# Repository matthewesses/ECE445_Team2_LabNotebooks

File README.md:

# ECE445 Team 2's Lab Notebooks
Lab Notebook repository for Team 2 for ECE 445 at UIUC

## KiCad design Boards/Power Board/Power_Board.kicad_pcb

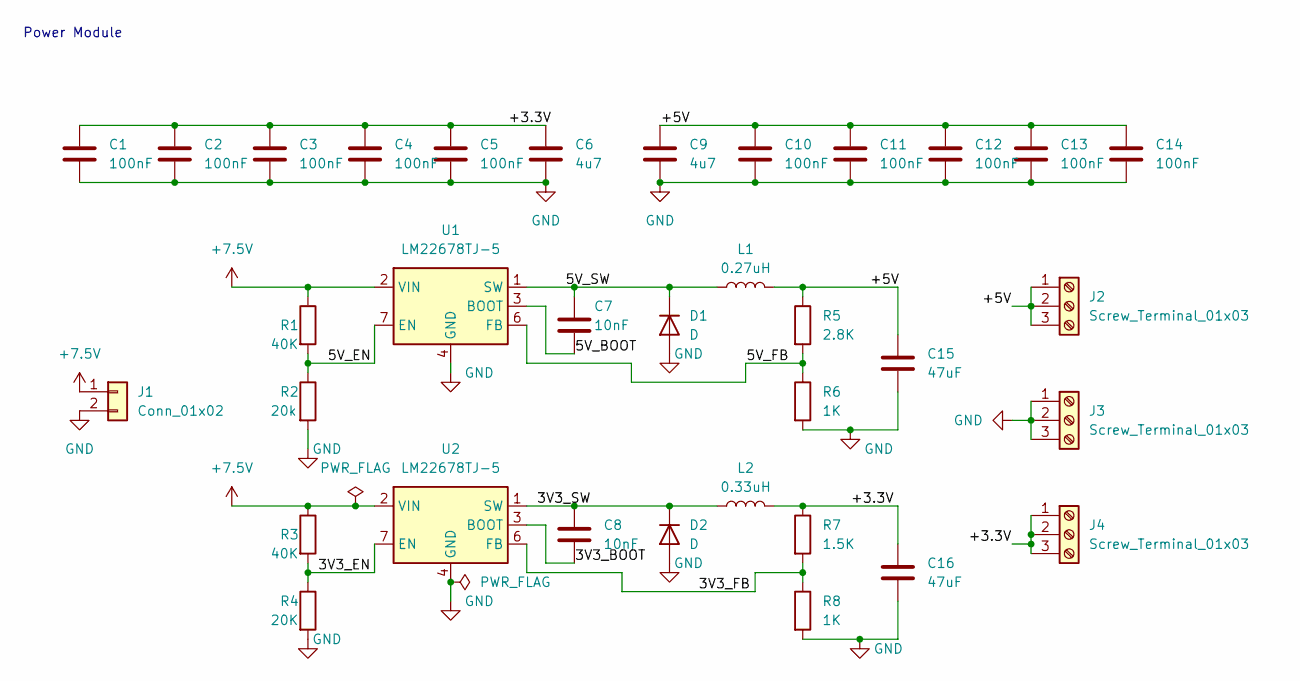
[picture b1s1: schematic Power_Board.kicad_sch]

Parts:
C1, C2, C3, C4, C5, C10, C11, C12, C13, C14: 100nF; C_0805_2012Metric_Pad1.18x1.45mm_HandSolder
C6, C9: 4u7; C_0805_2012Metric_Pad1.18x1.45mm_HandSolder
C7, C8: 10nF; C_0805_2012Metric_Pad1.18x1.45mm_HandSolder
C15, C16: 47uF; C_0805_2012Metric_Pad1.18x1.45mm_HandSolder
D1, D2: D; D_1210_3225Metric_Pad1.42x2.65mm_HandSolder
J1: Conn_01x02; AMASS_XT60-M_1x02_P7.20mm_Vertical
J2, J3, J4: Screw_Terminal_01x03; PinSocket_1x03_P2.54mm_Vertical
L1: 0.27uH; L_1210_3225Metric
L2: 0.33uH; L_1210_3225Metric
R1, R3: 40K; R_0805_2012Metric_Pad1.20x1.40mm_HandSolder
R2: 20k; R_0805_2012Metric_Pad1.20x1.40mm_HandSolder
R4: 20K; R_0805_2012Metric_Pad1.20x1.40mm_HandSolder
R5: 2.8K; R_0805_2012Metric_Pad1.20x1.40mm_HandSolder
R6, R8: 1K; R_0805_2012Metric_Pad1.20x1.40mm_HandSolder
R7: 1.5K; R_0805_2012Metric_Pad1.20x1.40mm_HandSolder
U1, U2: LM22678TJ-5; TO-263-7_TabPin8

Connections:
+7.5V: J1.1, R1.1, R3.1, U1.2 (VIN), U2.2 (VIN)
/3V3_BOOT: C8.2, U2.3 (BOOT)
/3V3_EN: R3.2, R4.1, U2.7 (EN)
/3V3_FB: R7.2, R8.1, U2.6 (FB)
/3V3_SW: C8.1, D2.1 (K), L2.1, U2.1 (SW)
/5V_BOOT: C7.2, U1.3 (BOOT)
/5V_EN: R1.2, R2.1, U1.7 (EN)
/5V_FB: R5.2, R6.1, U1.6 (FB)
/5V_SW: C7.1, D1.1 (K), L1.1, U1.1 (SW)
/+3.3V: C1.1, C2.1, C3.1, C4.1, C5.1, C6.1, C16.1, J4.1, J4.2, J4.3, L2.2, R7.1
/+5V: C9.1, C10.1, C11.1, C12.1, C13.1, C14.1, C15.1, J2.1, J2.2, J2.3, L1.2, R5.1
GND: C1.2, C2.2, C3.2, C4.2, C5.2, C6.2, C9.2, C10.2, C11.2, C12.2, C13.2, C14.2, C15.2, C16.2, D1.2 (A), D2.2 (A), J1.2, J3.1, J3.2, J3.3, R2.2, R4.2, R6.2, R8.2, U1.4 (GND), U1.8 (GND), U2.4 (GND), U2.8 (GND)

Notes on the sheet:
Power Module

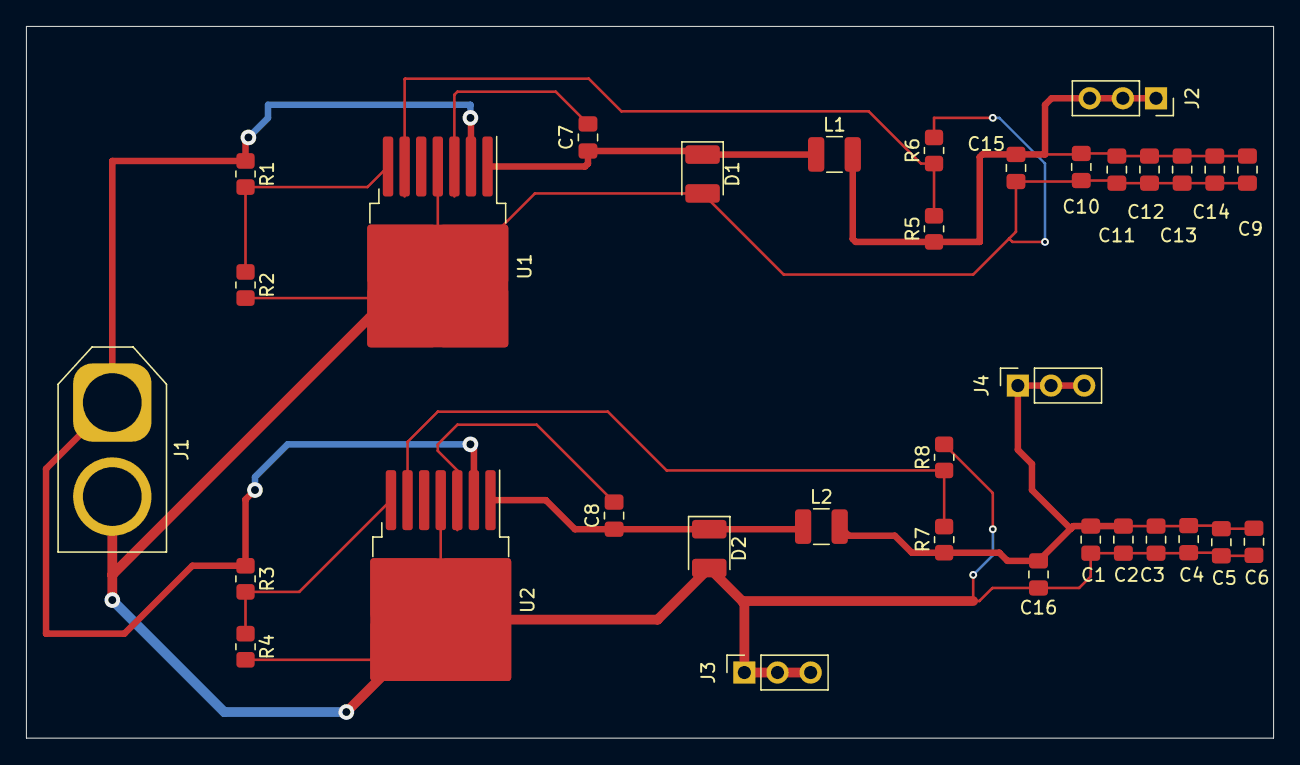
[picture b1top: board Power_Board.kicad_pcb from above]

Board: 2 copper layers, 95.5 x 54.5 mm, 34 parts (0 on the bottom side), 12 nets.

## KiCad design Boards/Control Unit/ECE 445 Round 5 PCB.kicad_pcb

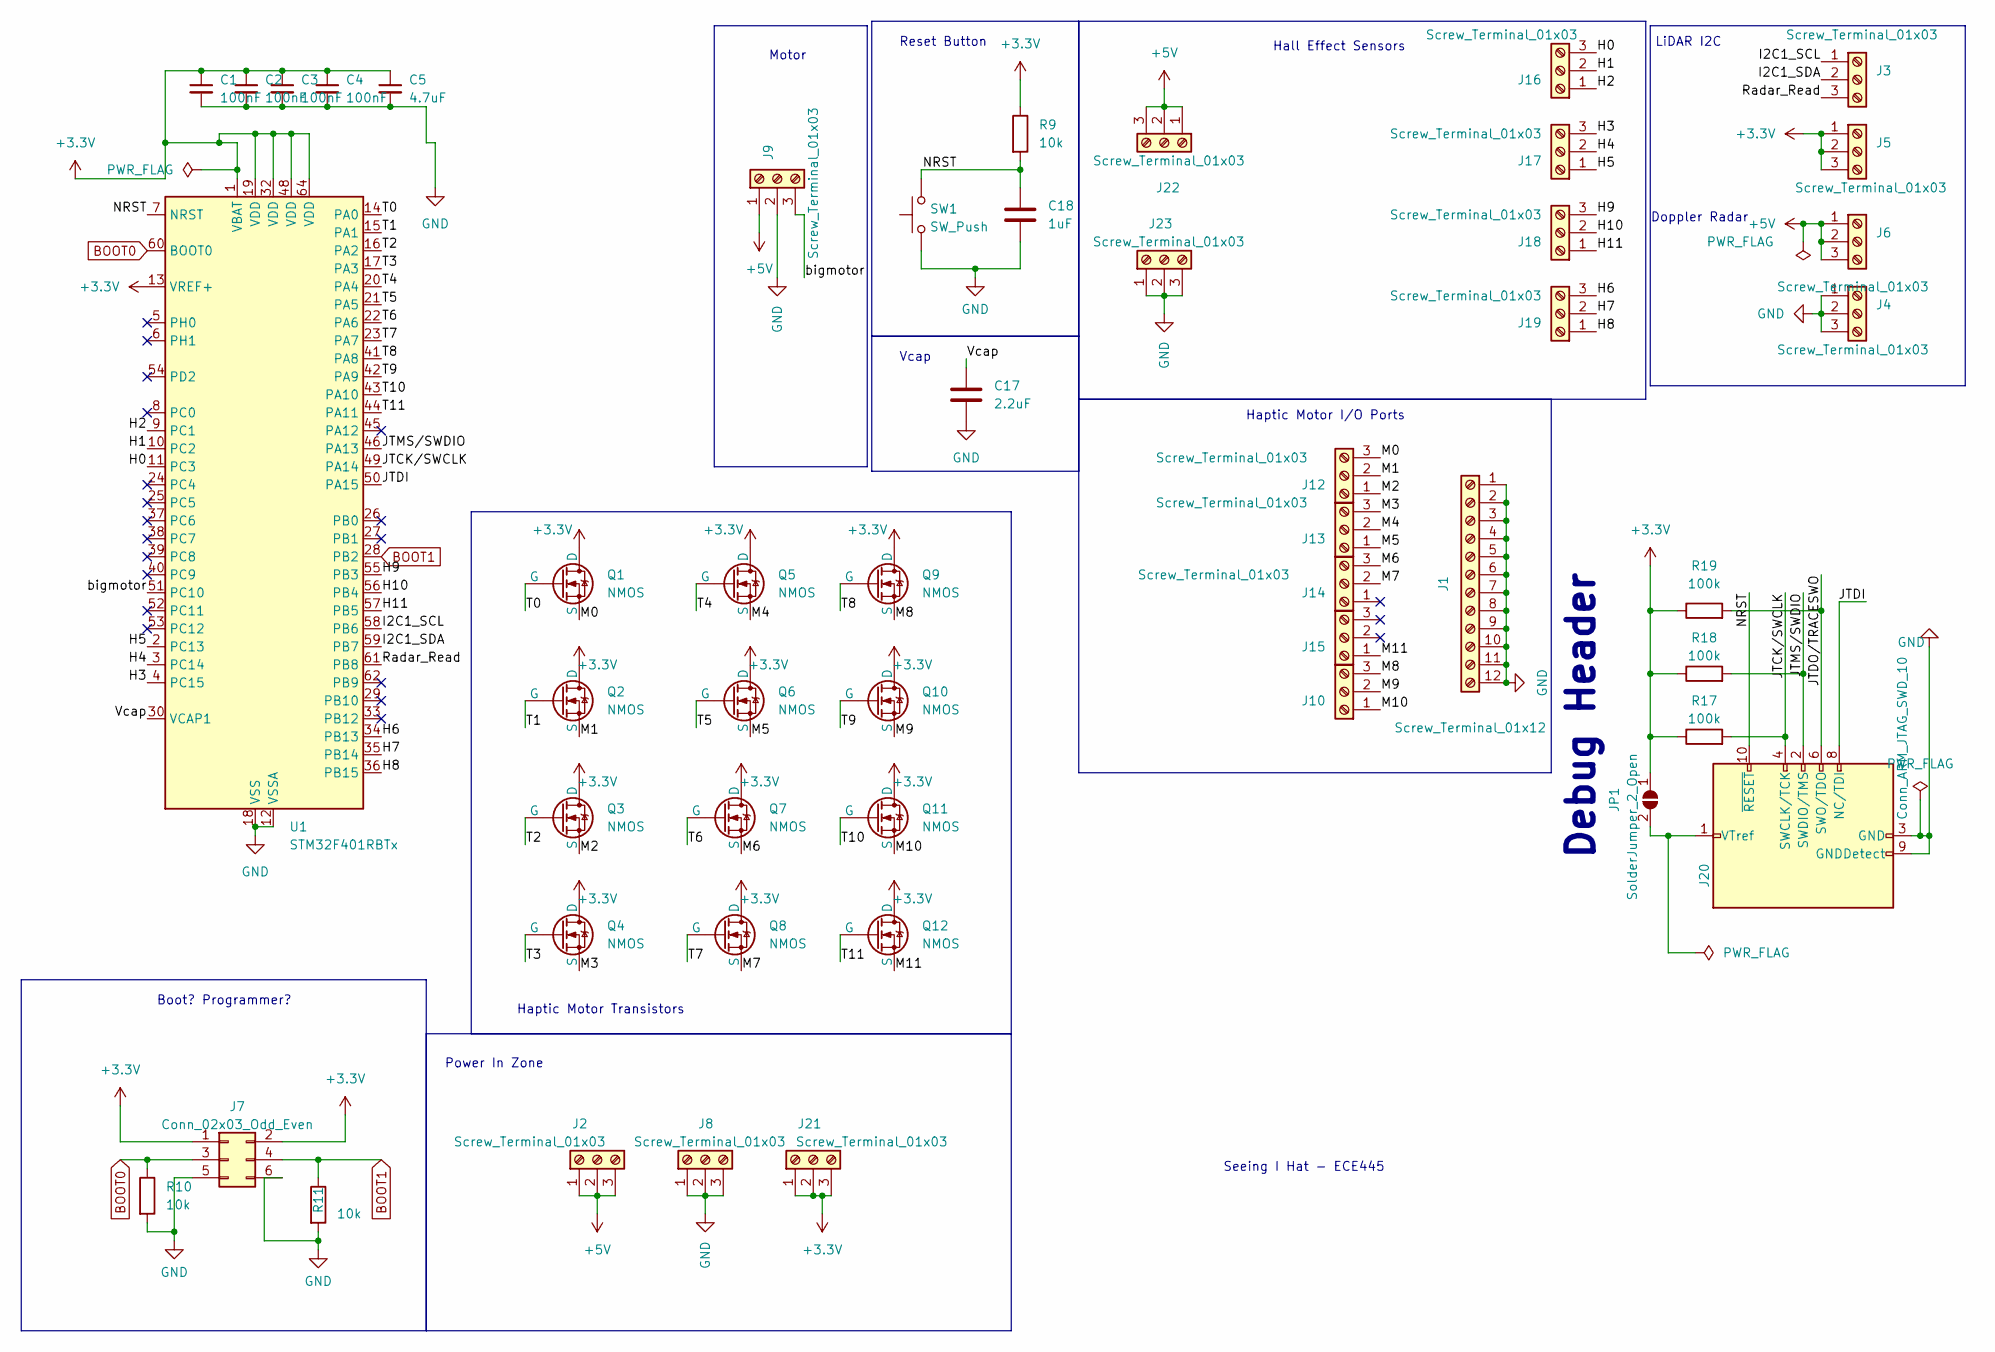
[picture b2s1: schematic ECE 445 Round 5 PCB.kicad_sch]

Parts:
C1, C2, C3, C4: 100nF; C_0805_2012Metric_Pad1.18x1.45mm_HandSolder
C5: 4.7uF; C_0805_2012Metric_Pad1.18x1.45mm_HandSolder
C17: 2.2uF; C_0805_2012Metric_Pad1.18x1.45mm_HandSolder
C18: 1uF; C_0805_2012Metric_Pad1.18x1.45mm_HandSolder
J1: Screw_Terminal_01x12; PinSocket_1x12_P2.54mm_Vertical
J2, J3, J4, J5, J6, J8, J9, J10, J12, J13, J14, J15, J16, J17, J18, J19, J21, J22, J23: Screw_Terminal_01x03; PinSocket_1x03_P2.54mm_Vertical
J7: Conn_02x03_Odd_Even; PinSocket_2x03_P2.54mm_Vertical
J20: Conn_ARM_JTAG_SWD_10; IDC-Header_2x05_P2.54mm_Vertical
JP1: SolderJumper_2_Open; SolderJumper-2_P1.3mm_Open_TrianglePad1.0x1.5mm
Q1, Q2, Q3, Q4, Q5, Q6, Q7, Q8, Q9, Q10, Q11, Q12: NMOS; SOT-23-3
R9, R10, R11: 10k; R_0805_2012Metric_Pad1.20x1.40mm_HandSolder
R17, R18, R19: 100k; R_0805_2012Metric_Pad1.20x1.40mm_HandSolder
SW1: SW_Push; SW_SPST_B3S-1000
U1: STM32F401RBTx; LQFP-64_10x10mm_P0.5mm

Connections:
+3.3V: C1.1, C2.1, C3.1, C4.1, C5.1, J5.1, J5.2, J5.3, J7.1, J7.2, J21.1, J21.2, J21.3, JP1.1 (A), Q1.1 (D), Q2.1 (D), Q3.1 (D), Q4.1 (D), Q5.1 (D), Q6.1 (D), Q7.1 (D), Q8.1 (D), Q9.1 (D), Q10.1 (D), Q11.1 (D), Q12.1 (D), R9.1, R17.1, R18.1, R19.1, U1.1 (VBAT), U1.13 (VREF+), U1.19 (VDD), U1.32 (VDD), U1.48 (VDD), U1.64 (VDD)
+5V: J2.1, J2.2, J2.3, J6.1, J6.2, J6.3, J9.1, J22.1, J22.2, J22.3
/H0: J16.3, U1.11 (PC3)
/H1: J16.2, U1.10 (PC2)
/H2: J16.1, U1.9 (PC1)
/H3: J17.3, U1.4 (PC15)
/H4: J17.2, U1.3 (PC14)
/H5: J17.1, U1.2 (PC13)
/H6: J19.3, U1.34 (PB13)
/H7: J19.2, U1.35 (PB14)
/H8: J19.1, U1.36 (PB15)
/H9: J18.3, U1.55 (PB3)
/H10: J18.2, U1.56 (PB4)
/H11: J18.1, U1.57 (PB5)
/I2C1_SCL: J3.1, U1.58 (PB6)
/I2C1_SDA: J3.2, U1.59 (PB7)
/JTCK/SWCLK: J20.4 (SWCLK/TCK), R17.2, U1.49 (PA14)
/JTDI: J20.8 (NC/TDI), U1.50 (PA15)
/JTDO/TRACESWO: J20.6 (SWO/TDO), R19.2
/JTMS/SWDIO: J20.2 (SWDIO/TMS), R18.2, U1.46 (PA13)
/M0: J12.3, Q1.3 (S)
/M1: J12.2, Q2.3 (S)
/M2: J12.1, Q3.3 (S)
/M3: J13.3, Q4.3 (S)
/M4: J13.2, Q5.3 (S)
/M5: J13.1, Q6.3 (S)
/M6: J14.3, Q7.3 (S)
/M7: J14.2, Q8.3 (S)
/M8: J10.3, Q9.3 (S)
/M9: J10.2, Q10.3 (S)
/M10: J10.1, Q11.3 (S)
/M11: J15.1, Q12.3 (S)
/NRST: C18.1, J20.10 (~RESET), R9.2, SW1.2, U1.7 (NRST)
/Radar_Read: J3.3, U1.61 (PB8)
/T0: Q1.2 (G), U1.14 (PA0)
/T1: Q2.2 (G), U1.15 (PA1)
/T2: Q3.2 (G), U1.16 (PA2)
/T3: Q4.2 (G), U1.17 (PA3)
/T4: Q5.2 (G), U1.20 (PA4)
/T5: Q6.2 (G), U1.21 (PA5)
/T6: Q7.2 (G), U1.22 (PA6)
/T7: Q8.2 (G), U1.23 (PA7)
/T8: Q9.2 (G), U1.41 (PA8)
/T9: Q10.2 (G), U1.42 (PA9)
/T10: Q11.2 (G), U1.43 (PA10)
/T11: Q12.2 (G), U1.44 (PA11)
/Vcap: C17.1, U1.30 (VCAP1)
/bigmotor: J9.3, U1.51 (PC10)
BOOT0: J7.3, R10.1, U1.60 (BOOT0)
BOOT1: J7.4, R11.1, U1.28 (PB2)
GND: C1.2, C2.2, C3.2, C4.2, C5.2, C17.2, C18.2, J1.1, J1.2, J1.3, J1.4, J1.5, J1.6, J1.7, J1.8, J1.9, J1.10, J1.11, J1.12, J4.1, J4.2, J4.3, J7.5, J7.6, J8.1, J8.2, J8.3, J9.2, J20.3 (GND), J20.5 (GND), J20.9 (GNDDetect), J23.1, J23.2, J23.3, R10.2, R11.2, SW1.1, U1.12 (VSSA), U1.18 (VSS), U1.31 (VSS), U1.47 (VSS), U1.63 (VSS)
unnamed: J20.1 (VTref), JP1.2 (B)

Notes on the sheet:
Boot? Programmer?
Seeing I Hat - ECE445
Haptic Motor I/O Ports
Debug Header
Motor
Doppler Radar
Reset Button
LiDAR I2C
Power In Zone
Vcap
Hall Effect Sensors
Haptic Motor Transistors

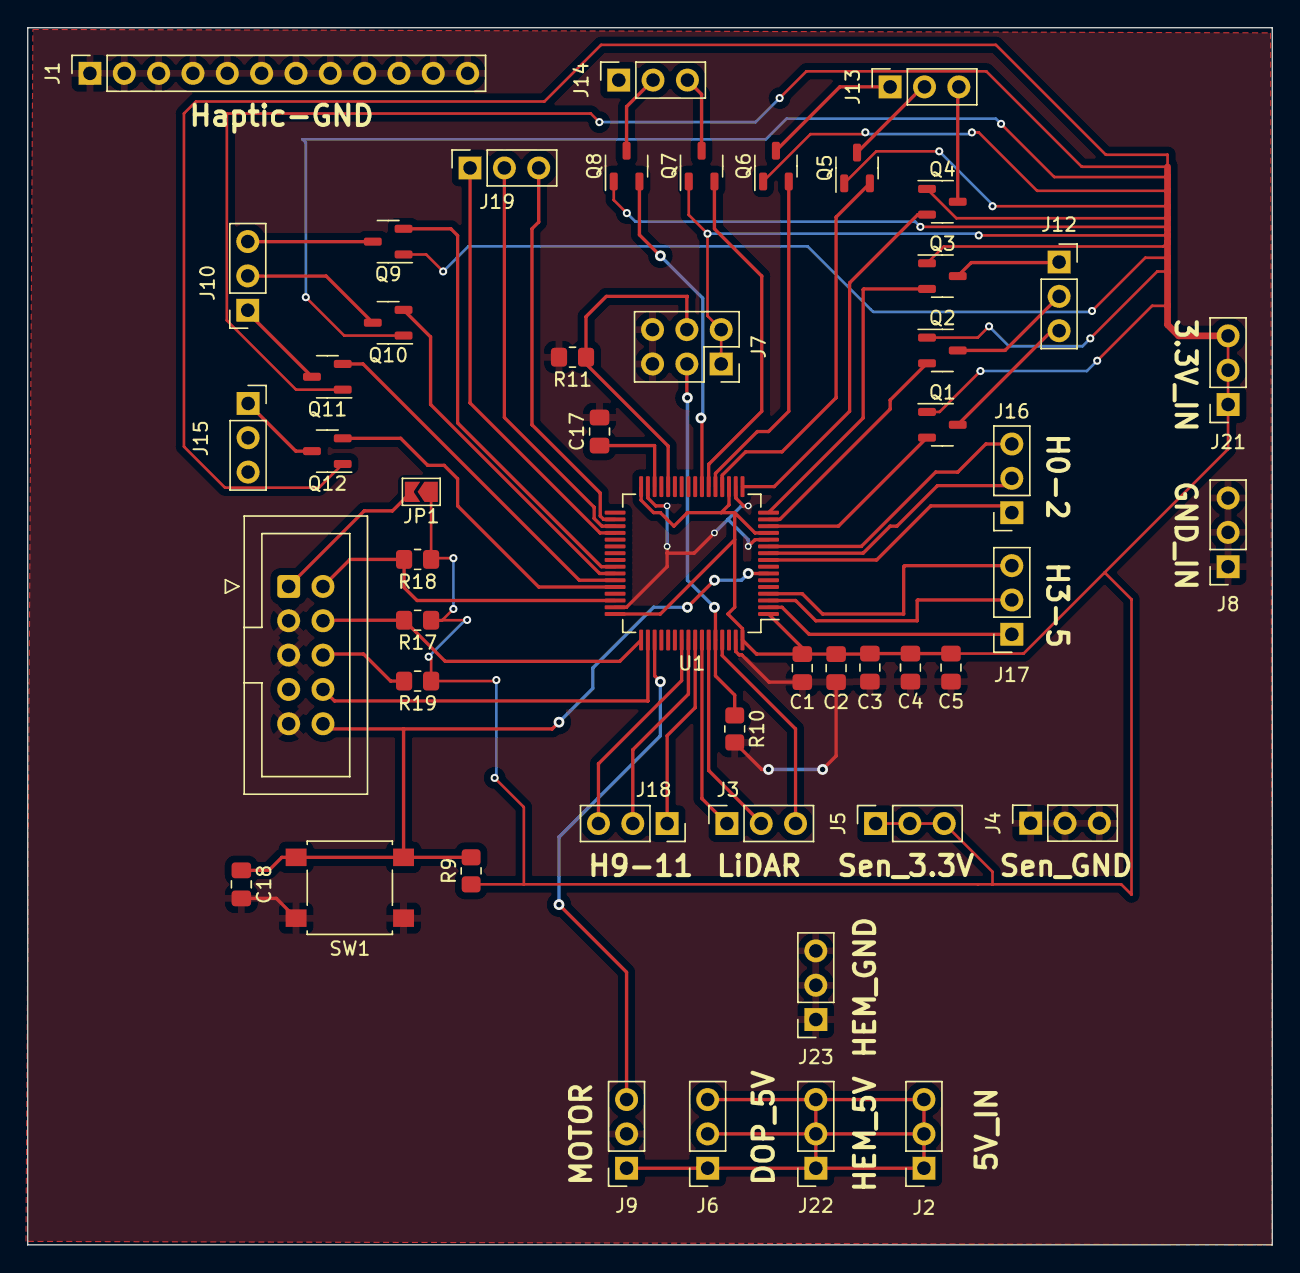
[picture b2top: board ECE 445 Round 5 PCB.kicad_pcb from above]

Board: 2 copper layers, 92.1 x 90.0 mm, 50 parts (0 on the bottom side), 52 nets.

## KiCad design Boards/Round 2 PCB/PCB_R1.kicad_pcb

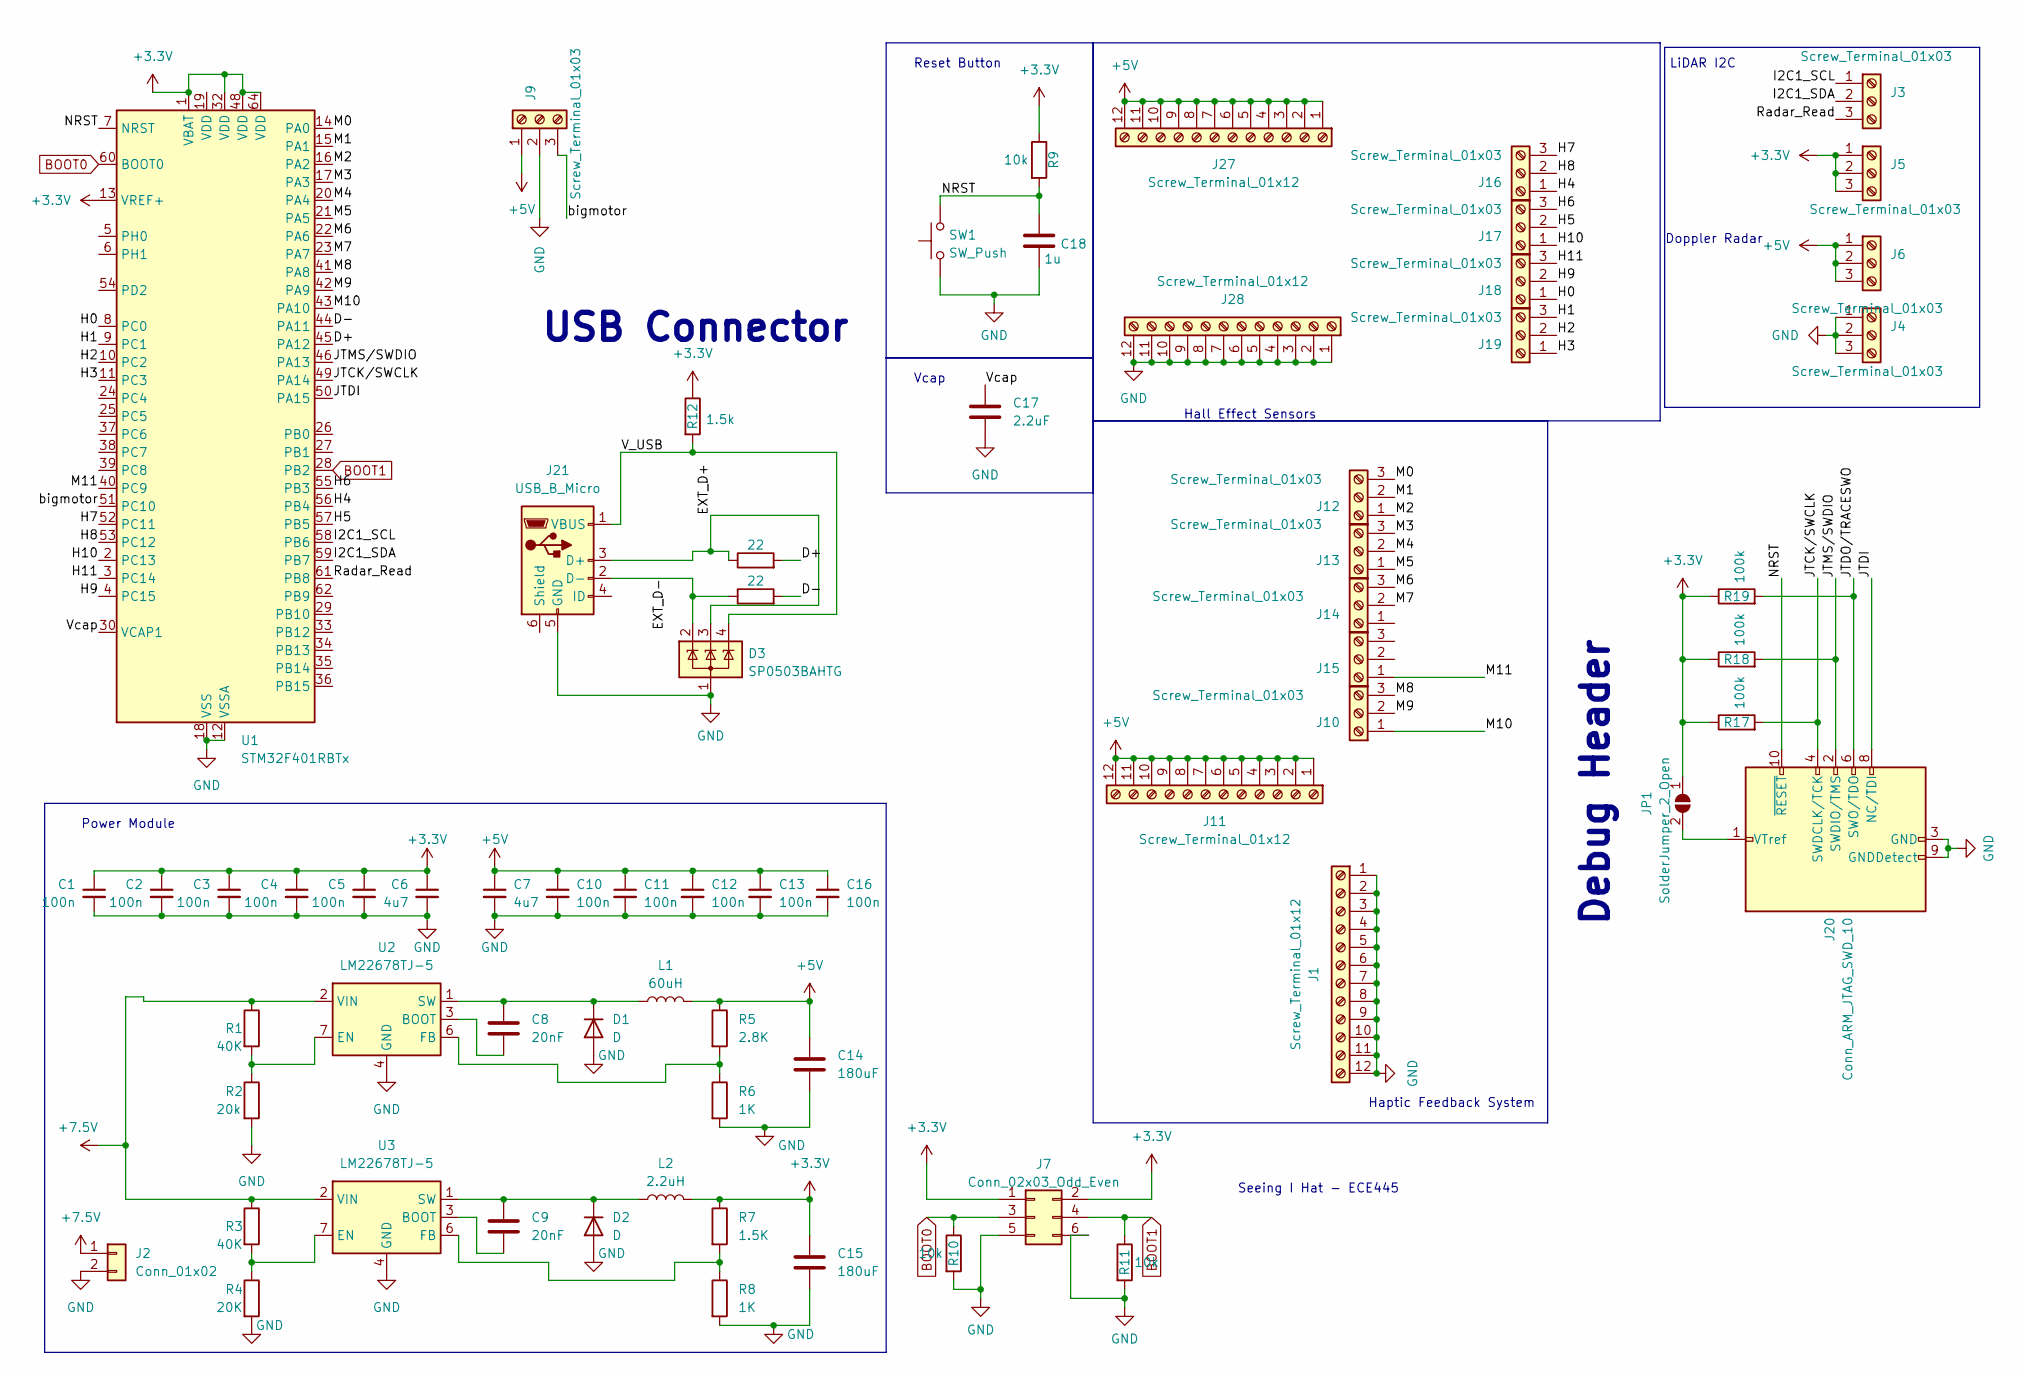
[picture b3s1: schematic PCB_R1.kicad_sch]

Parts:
C1, C2, C3, C4, C5, C10, C11, C12, C13, C16: 100n; C_0805_2012Metric_Pad1.18x1.45mm_HandSolder; LCSC Part # C1525
C6, C7: 4u7; C_0805_2012Metric_Pad1.18x1.45mm_HandSolder; LCSC Part # C19666
C8, C9: 20nF; C_0805_2012Metric_Pad1.18x1.45mm_HandSolder
C14, C15: 180uF; C_0805_2012Metric_Pad1.18x1.45mm_HandSolder
C17: 2.2uF; C_0805_2012Metric_Pad1.18x1.45mm_HandSolder
C18: 1u; C_0805_2012Metric_Pad1.18x1.45mm_HandSolder
D1, D2: D; D_1210_3225Metric_Pad1.42x2.65mm_HandSolder
D3: SP0503BAHTG; SOT-143
J1, J11, J27, J28: Screw_Terminal_01x12; PinSocket_1x12_P2.54mm_Vertical
J2: Conn_01x02; AMASS_XT60-M_1x02_P7.20mm_Vertical
J3, J4, J5, J6, J9, J10, J12, J13, J14, J15, J16, J17, J18, J19: Screw_Terminal_01x03; PinSocket_1x03_P2.54mm_Vertical
J7: Conn_02x03_Odd_Even; PinSocket_2x03_P2.54mm_Vertical
J20: Conn_ARM_JTAG_SWD_10; IDC-Header_2x05_P2.54mm_Vertical
J21: USB_B_Micro; USB_Micro-B_Molex_47346-0001
JP1: SolderJumper_2_Open; SolderJumper-2_P1.3mm_Open_TrianglePad1.0x1.5mm
L1: 60uH; L_1210_3225Metric
L2: 2.2uH; L_1210_3225Metric
R1, R3: 40K; R_0805_2012Metric_Pad1.20x1.40mm_HandSolder
R2: 20k; R_0805_2012Metric_Pad1.20x1.40mm_HandSolder
R4: 20K; R_0805_2012Metric_Pad1.20x1.40mm_HandSolder
R5: 2.8K; R_0805_2012Metric_Pad1.20x1.40mm_HandSolder
R6, R8: 1K; R_0805_2012Metric_Pad1.20x1.40mm_HandSolder
R7: 1.5K; R_0805_2012Metric_Pad1.20x1.40mm_HandSolder
R9, R10, R11: 10k; R_0805_2012Metric_Pad1.20x1.40mm_HandSolder
R12: 1.5k; R_0805_2012Metric
R13, R15: 22; R_0603_1608Metric
R17, R18, R19: 100k; R_0805_2012Metric_Pad1.20x1.40mm_HandSolder
SW1: SW_Push; SW_SPST_B3S-1000
U1: STM32F401RBTx; LQFP-64_10x10mm_P0.5mm
U2, U3: LM22678TJ-5; TO-263-7_TabPin8

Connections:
+7.5V: J2.1, R1.1, R3.1, U2.2 (VIN), U3.2 (VIN)
/D+: R13.2, U1.45 (PA12)
/D-: R15.2, U1.44 (PA11)
/EXT_D+: D3.3 (K), J21.3 (D+), R13.1
/EXT_D-: D3.2 (K), J21.2 (D-), R15.1
/H0: J18.1, U1.8 (PC0)
/H1: J19.3, U1.9 (PC1)
/H2: J19.2, U1.10 (PC2)
/H3: J19.1, U1.11 (PC3)
/H4: J16.1, U1.56 (PB4)
/H5: J17.2, U1.57 (PB5)
/H6: J17.3, U1.55 (PB3)
/H7: J16.3, U1.52 (PC11)
/H8: J16.2, U1.53 (PC12)
/H9: J18.2, U1.4 (PC15)
/H10: J17.1, U1.2 (PC13)
/H11: J18.3, U1.3 (PC14)
/I2C1_SCL: J3.1, U1.58 (PB6)
/I2C1_SDA: J3.2, U1.59 (PB7)
/JTCK/SWCLK: J20.4 (SWDCLK/TCK), R17.2, U1.49 (PA14)
/JTDI: J20.8 (NC/TDI), U1.50 (PA15)
/JTDO/TRACESWO: J20.6 (SWO/TDO), R19.2
/JTMS/SWDIO: J20.2 (SWDIO/TMS), R18.2, U1.46 (PA13)
/M0: J12.3, U1.14 (PA0)
/M1: J12.2, U1.15 (PA1)
/M2: J12.1, U1.16 (PA2)
/M3: J13.3, U1.17 (PA3)
/M4: J13.2, U1.20 (PA4)
/M5: J13.1, U1.21 (PA5)
/M6: J14.3, U1.22 (PA6)
/M7: J14.2, U1.23 (PA7)
/M8: J10.3, U1.41 (PA8)
/M9: J10.2, U1.42 (PA9)
/M10: J10.1, U1.43 (PA10)
/M11: J15.1, U1.40 (PC9)
/NRST: C18.1, J20.10 (~RESET), R9.2, SW1.2, U1.7 (NRST)
/Radar_Read: J3.3, U1.61 (PB8)
/V_USB: D3.4 (K), J21.1 (VBUS), R12.2
/Vcap: C17.1, U1.30 (VCAP1)
/bigmotor: J9.3, U1.51 (PC10)
BOOT0: J7.3, R10.1, U1.60 (BOOT0)
BOOT1: J7.4, R11.1, U1.28 (PB2)
GND: C1.2, C2.2, C3.2, C4.2, C5.2, C6.2, C7.2, C10.2, C11.2, C12.2, C13.2, C14.2, C15.2, C16.2, C17.2, C18.2, D1.2 (A), D2.2 (A), D3.1 (A), J1.1, J1.2, J1.3, J1.4, J1.5, J1.6, J1.7, J1.8, J1.9, J1.10, J1.11, J1.12, J2.2, J4.1, J4.2, J4.3, J7.5, J7.6, J9.2, J20.3 (GND), J20.5 (GND), J20.9 (GNDDetect), J21.5 (GND), J28.1, J28.2, J28.3, J28.4, J28.5, J28.6, J28.7, J28.8, J28.9, J28.10, J28.11, J28.12, R2.2, R4.2, R6.2, R8.2, R10.2, R11.2, SW1.1, U1.12 (VSSA), U1.18 (VSS), U1.31 (VSS), U1.47 (VSS), U1.63 (VSS), U2.4 (GND), U2.8 (GND), U3.4 (GND), U3.8 (GND)
unnamed: C8.1, D1.1 (K), L1.1, U2.1 (SW)
unnamed: C9.1, D2.1 (K), L2.1, U3.1 (SW)
unnamed: J20.1 (VTref), JP1.2 (B)
unnamed: C8.2, U2.3 (BOOT)
unnamed: R1.2, R2.1, U2.7 (EN)
unnamed: R5.2, R6.1, U2.6 (FB)
unnamed: C9.2, U3.3 (BOOT)
unnamed: R3.2, R4.1, U3.7 (EN)
unnamed: R7.2, R8.1, U3.6 (FB)

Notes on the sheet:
Seeing I Hat - ECE445
Debug Header
Power Module
Haptic Feedback System
Doppler Radar
Reset Button
USB Connector
LiDAR I2C
Vcap
Hall Effect Sensors

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
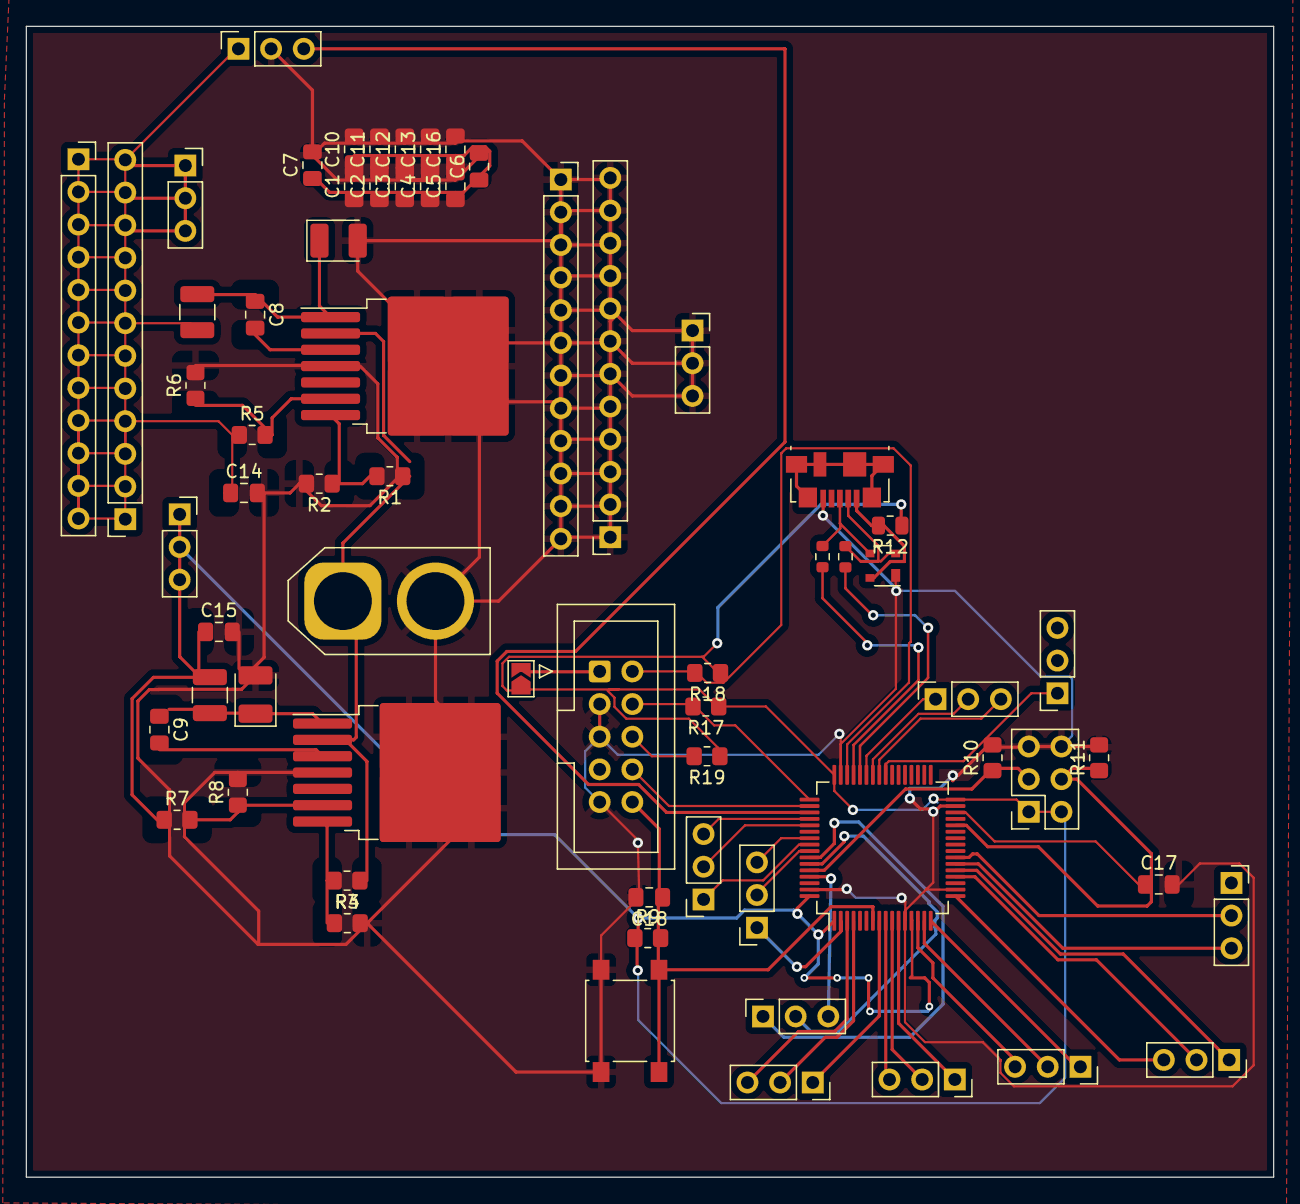
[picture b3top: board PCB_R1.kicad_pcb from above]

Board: 2 copper layers, 97.0 x 89.5 mm, 67 parts (0 on the bottom side), 55 nets.

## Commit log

2024-02-06 Added individual folders
2024-02-06 fixed file system
2024-03-17 Moving PCB version control to github
    That got ugly, we now have a folder for the complete schematic, and the round 1 PCB Files.
2024-03-17 Power System Update
    added component values to the power system, and fixed ground nets
2024-03-17 Inductor update
    oops, I forgot the inductor values again
2024-03-18 Misc updates from 3/17/24
    Touched up a few really minor things while I was doing the parts list
2024-03-18 PCB Design contraints
    Updated and tested width and clearene constraints and everything was ok, one unconnected thing. Footprints not updated
2024-03-18 fixed PCB contraints and re-routed something that broke
    yea, that
2024-03-18 R1 - no builder errors
    woot woot
2024-03-18 r1 SMD footprint updates
    changed component footprints on the board and schematic to use free smd components
2024-03-19 Create I2C Communication Notes
2024-03-19 Resistor 0805 update
    all resistors and capacitors are 0805 now, thanks Dad
2024-03-19 potentially useful link
2024-03-21 Round 2 Init
    ROUND 2, START!
2024-03-23 ground layer test
    placed all transistors, about to delete all ground connections
2024-03-23 transistor routing
    3.3V pins on all transistors are routed. Should increase net width of 3.3V bus
2024-03-23 error handeling
    fixed all errors after adding transistors and general cleanup
2024-03-23 power bus width update
    Updated power bus width going to each of the motors to reduce board heating
2024-03-24 adding notes on I2C
2024-03-25 placeholder file for i2c
2024-03-25 replace stm32 i2c file
2024-03-25 add new i2c file
2024-03-26 move to different computer for testing
2024-03-27 debugging program from adafruit (checks for lidar)
2024-03-27 added webpage link
2024-03-27 HVPS Update
    changed HVPS components to increase maximum current from 0.5A to 1A
2024-03-29 reading zero values from distance registers
2024-03-29 we getting distances WOOO
2024-04-09 Power Board Seperate Edition
    I wanna go to bed
2024-04-09 current version of separate control unit
2024-04-09 Create new folder for control unit
2024-04-09 power board connectors and ERC changes
    reeeeeeeeeeeeeeeeeeeee
2024-04-09 control unit ERC Changes part 1
    resistors need changes
2024-04-09 control unit pt2 all errors/warnings fixed
2024-04-09 added pwr_flags to resolve errors
2024-04-09 removed extranious 5v power buses
    hall effect module is pretty nice
2024-04-09 routed except gnd and vcc
    that was rough
2024-04-09 power routing example
    oop
2024-04-09 current control unit
2024-04-09 passes drc
    aaaaaaaaaaaaaaaaaa
2024-04-09 didnt save,
    sad
2024-04-09 constrained
    let's try this
2024-04-09 power system size decrease
    a
2024-04-13 first draft of code for hall effect sensors on pcb
2024-04-13 stencil hall effect code devboard
2024-04-13 full code drafts for pcb and devboard
2024-04-13 uploaded first draft of full code
2024-04-16 added pin assignments
2024-04-16 added pin assignments for hall and motor
2024-04-22 code w/stepper motor and one hall effect
2024-04-24 code w/includes
2024-04-25 full working code yay
2024-04-25 final documents
    created final documents
2024-04-26 presentatino
    prezent
2024-04-26 added doppler
2024-04-26 added doppler w/print
2024-04-26 updates
    updoot
2024-04-26 final demo code
2024-04-26 Final Presentation Outlined
    this is it
2024-04-28 design sections, power, haptic, scanning
    progess
2024-04-28 verification section
    verification section draft
2024-04-28 BOM and Power Details
    stuff
2024-04-28 present
    LTG Speach
2024-04-29 presentation as of 4/28 afternoon
2024-05-02 final code
